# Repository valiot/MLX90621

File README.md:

### MLX90621 Arduino and Processing example code

Arduino and Processing code for the Melexis [MLX90621](http://www.melexis.com/Infrared-Thermometer-Sensors/Infrared-Thermometer-Sensors/Low-noise-high-speed-16x4-Far-Infrared-array-823.aspx) 16x4 thermopile array.

Includes R script to parse data files (which can be exported by Processing visualizer).

The MLX90621 FIRray temperature sensing device from Melexis utilizes the company’s non-contact temperature measurement technology to create a highly cost-effective thermography solution. Covering a -20°C to 300°C temperature range, this 16 x 4 element far infrared (FIR) thermopile sensor array produces a map of heat values for the target area in real time, avoiding the need to scan the area with a single point sensor or use an expensive microbolometer device.

In use in VU and Tilburg University temperature [cry detection project](http://www.pavlov.io/2015/07/01/detecting-crying-eyes/).

Implements MaxBot's MLX90621 [Arduino library](http://forum.arduino.cc/index.php?topic=126244.0) patched with KMoto's [minor change](http://forum.arduino.cc/index.php?topic=126244.msg2307588#msg2307588) in defaultConfig_H.

Also makes use of [nox771's i2c_t3 enhanced Teensy 3 Wire library](https://github.com/nox771/i2c_t3). This library allows a [Teensy 3.1](https://www.pjrc.com/store/teensy31.html) Arduino compatible USB development board to communicate with the MLX90621 over I2C/TWI.

TODO 2015-10-25: Refactor and clean up Processing visualizer.

##### Screenshot

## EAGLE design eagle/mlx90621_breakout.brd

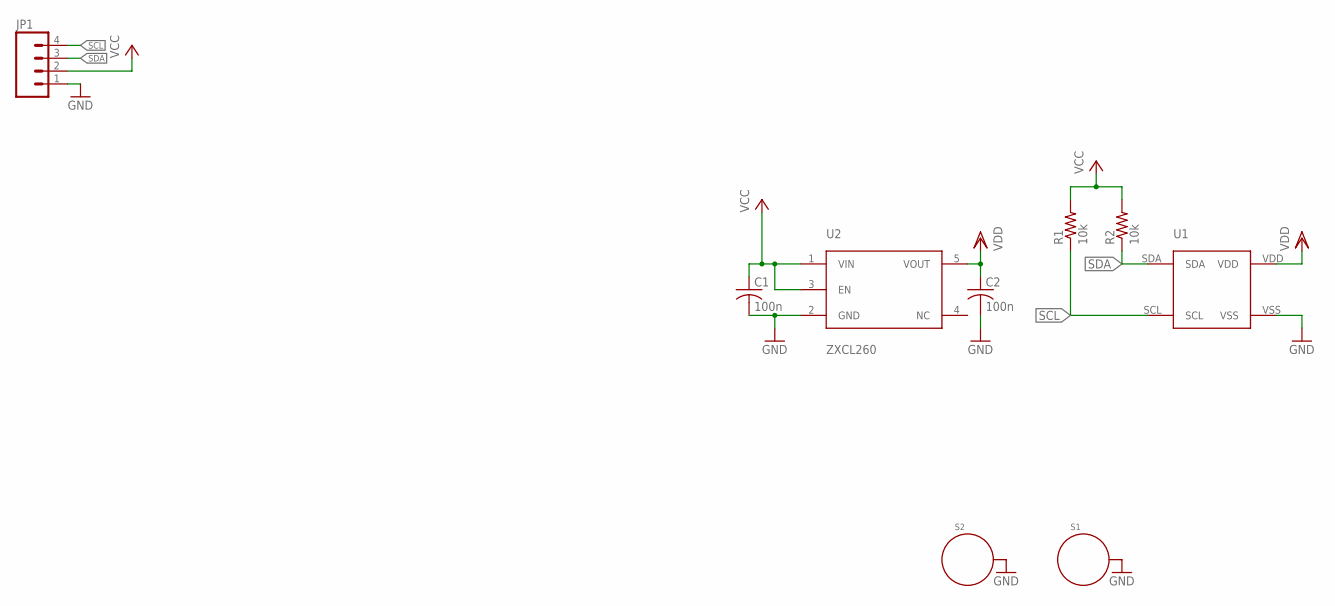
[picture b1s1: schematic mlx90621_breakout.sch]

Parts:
C1, C2: 100n; C0603
JP1: M04PTH; 1X04
R1, R2: 10k; R0603
S1, S2: STANDOFF_ELECTRICAL; STANDOFF-ELECTRICAL
U1: MLX90621BAD; MLX90621
U2: ZXCL260; VREG_SOT23-5

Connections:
GND: C1.2, C2.2, JP1.1, S1.P1, S2.P1, U1.VSS, U2.2 (GND)
SCL: JP1.4, R1.1, U1.SCL
SDA: JP1.3, R2.1, U1.SDA
VCC: C1.1, JP1.2, R1.2, R2.2, U2.1 (VIN), U2.3 (EN)
VDD: C2.1, U1.VDD, U2.5 (VOUT)

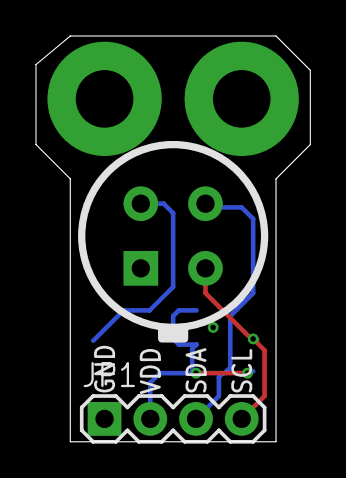
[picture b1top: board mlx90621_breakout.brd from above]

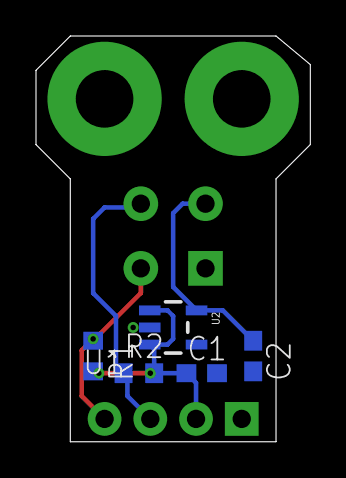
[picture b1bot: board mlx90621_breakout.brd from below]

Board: 2 copper layers, 15.2 x 22.5 mm, 9 parts (6 on the bottom side), 5 nets.

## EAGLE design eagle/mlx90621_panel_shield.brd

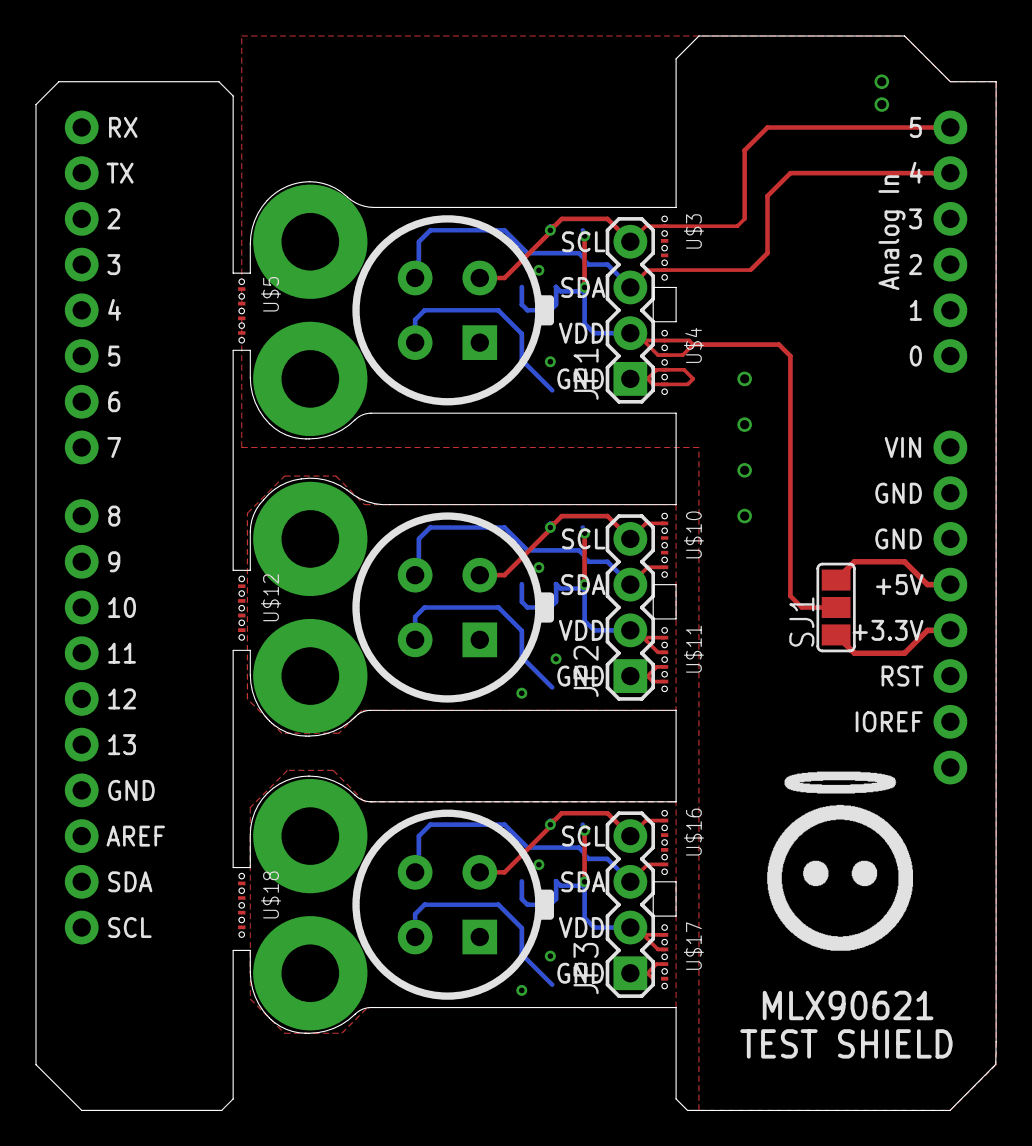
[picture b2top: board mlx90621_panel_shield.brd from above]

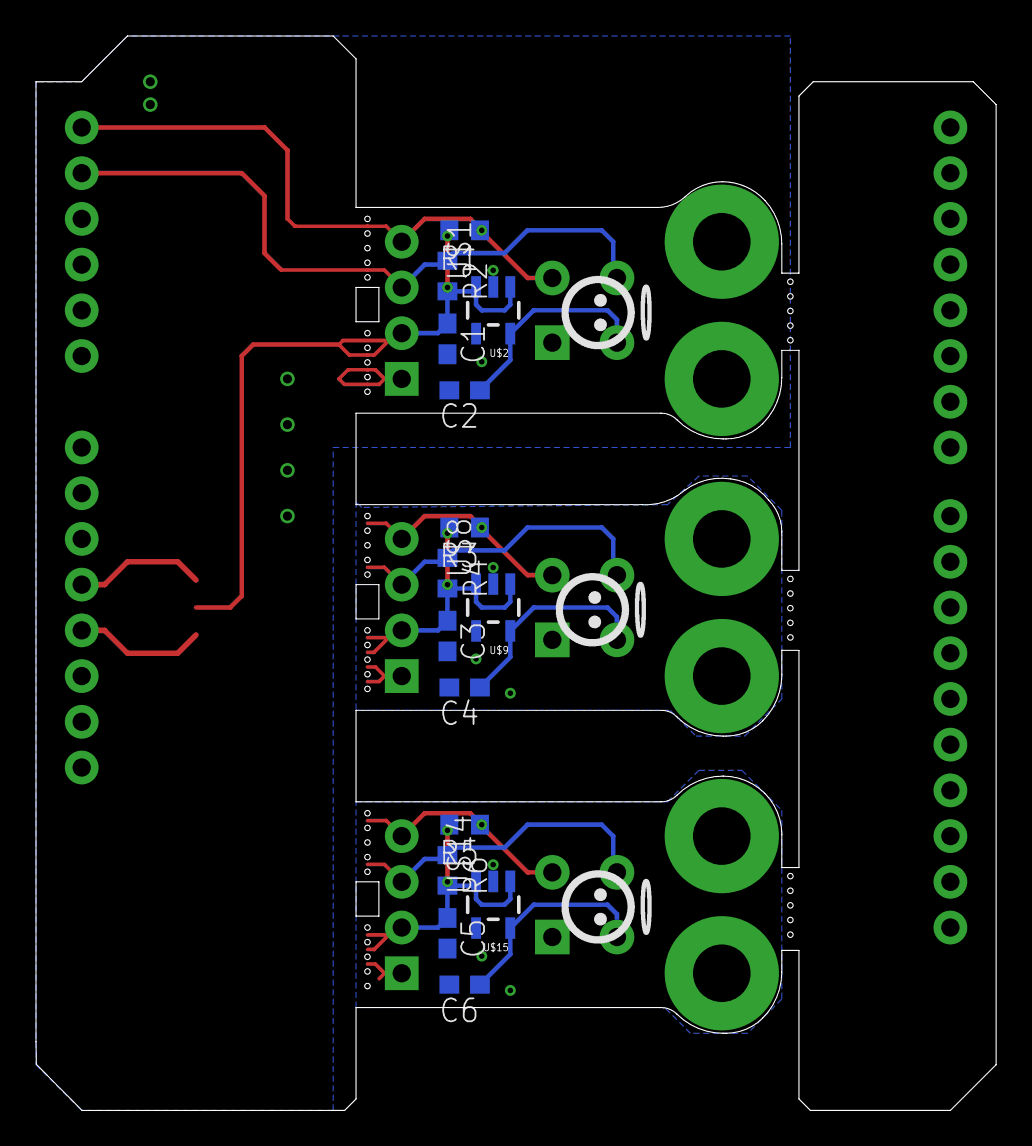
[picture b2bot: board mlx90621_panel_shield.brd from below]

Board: 2 copper layers, 53.3 x 59.7 mm, 42 parts (21 on the bottom side), 17 nets.

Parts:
C1, C2, C3, C4, C5, C6: 100n; C0603
E$1: DA_LOGO_10MM
E$2, E$3, E$4: DA_LOGO_5MM
J1: ARDUINO_R3_SHIELD; UNO_R3_SHIELD
JP1, JP2, JP3: 1X04
R1, R2, R3, R4, R5, R6: 10k; R0603
S1, S2, S3, S4, S5, S6: STANDOFF_ELECTRICAL; STANDOFF-ELECTRICAL
SJ1: SJ_2
U$1, U$8, U$14: MLX90621BAD; MLX90621
U$2, U$9, U$15: ZXCL260; VREG_SOT23-5
U$3, U$4, U$5, U$10, U$11, U$12, U$16, U$17, U$18: MOUSE-BITES-4

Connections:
+3V3: J1.3.3V, SJ1.1
+5V: J1.5V, SJ1.3
GND: C1.2, C2.2, J1.GND@0, J1.GND@1, JP1.1, S1.P1, S2.P1, U$1.VSS, U$2.2, U$4.3, U$4.4
GND1: C3.2, C4.2, JP2.1, S3.P1, S4.P1, U$8.VSS, U$9.2, U$11.3, U$11.4
GND2: C5.2, C6.2, JP3.1, S5.P1, S6.P1, U$14.VSS, U$15.2, U$17.3, U$17.4
SCL: J1.A5, JP1.4, R1.1, U$1.SCL, U$3.1
SCL1: JP2.4, R3.1, U$8.SCL, U$10.1
SCL2: JP3.4, R5.1, U$14.SCL, U$16.1
SDA: J1.A4, JP1.3, R2.1, U$1.SDA, U$3.4
SDA1: JP2.3, R4.1, U$8.SDA, U$10.4
SDA2: JP3.3, R6.1, U$14.SDA, U$16.4
VCC: C1.1, JP1.2, R1.2, R2.2, SJ1.2, U$2.1, U$2.3, U$4.1, U$4.2
VCC1: C3.1, JP2.2, R3.2, R4.2, U$9.1, U$9.3, U$11.1, U$11.2
VCC2: C5.1, JP3.2, R5.2, R6.2, U$15.1, U$15.3, U$17.1, U$17.2
VDD: C2.1, U$1.VDD, U$2.5
VDD1: C4.1, U$8.VDD, U$9.5
VDD2: C6.1, U$14.VDD, U$15.5

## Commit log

2017-08-20 Creada estructura del proyecto, basada en visualizador de ejemplo
2017-08-20 Modificado delay de Arduino
2017-08-20 Fix readme syntax
2017-08-21 Añadido gitignore
2017-08-21 modificado gitignore (Add jpg)
2017-08-22 Modificado readTemperatures por libreria de Longjos
2017-08-22 eliminado circuito de ejemplo incorrecto (jpg)
2017-08-22 Agregados a gitignore archivos backup de EAGLE
2017-08-23 Finalizado ruteo de MLX90621 en shield (x1)
2017-08-23 Finalizado diseño de panel shield
2017-08-23 añadida carpeta gerber a gitignore
2017-08-23 Añadida lib de logos de DA
2017-08-23 Añadidos logos a shield
2017-08-26 modificado .gitignore (ignorar gerbers de eagle)
2017-08-26 modificado .gitignore (ignora archivos gerber de eagle)
2017-08-27 Modificado baudrate en visualizador (ahora 115k2)
2017-08-27 Modificado baudrate en Arduino (ahora 115k2), modificados prints por blink de LED
2017-08-27 Añadida referencia para benchmark de funciones
2017-08-27 Modif libreria MLX para ir a 400kHz
2017-08-27 Tests de modificacion de resolucion a libreria (a mano)
2017-08-27 Correccion de factor K -> C (273.15) y prueba emisividad
2017-08-27 refactor checkConfig()
2017-08-28 Añadidas enumeraciones de resolucion y refresco a .h
2017-08-28 Añadidas propiedades y métodos de refresh, resolucion y emisividad a .h de sensor
2017-08-28 Implementados métodos de emisividad, refresh y resolucion en .cpp
2017-08-28 Actualizado ejemplo a nuevos métodos de la libreria de temperatura
2017-08-28 Modificado visualizador, ahora permite elegir rango de colores
2017-08-28 Mejorada visualizacion de gradiente
2017-08-28 Removida grasa de la interfaz (cuadros con promedios y umbrales)
2017-08-28 No guardar archivos por ahora y cambios en escala de color
2017-08-28 Eliminadas impresiones a serial innecesarias
2017-08-28 modificada resolucion de sensor de temperatura
2017-08-31 alarm visualizer
2017-08-31 Variables min mac configurables (teclas)
2017-09-12 Añadidas medidas a PCB
2017-09-12 Prueba de MOSFET vs calentador inductivo
2017-09-14 añadido BOM de eagle a gitignore
2017-09-14 eliminados archivos .txt innecesarios (outputs de visualizer)
2017-09-14 Eliminadas imports innecesarios del visualizador
2017-09-18 Prueba de corriente y PWM MOSFET
2017-09-18 Añadidas fotos de pruebas corriente
2017-09-23 Borrados archivos de tests de termopares (Movidos a otro repo)
2017-09-23 Modificado breakout de sensor MLX (Añadidos bValues)
2017-09-23 Modificada velocidad de comunicacion de sensor (4Hz a 8Hz)
2017-09-23 Modificada funcion de deteccion de puerto COM para aceptar puertos de Windows (COM)
2017-10-01 Add board image
2017-10-02 Add LICENSE
2017-10-07 añadido comentario inicial a headers
2017-10-08 prueba ems=0.1
2017-10-13 agregado linux a lista de sistemas soportados por el serial del visualizador
2017-10-14 emisividad 1.0
2018-05-21 cleaned PCB (Removed shield)
2018-05-21 cleaned board: Removed innecesary measures
2018-05-28 added measures and cleaned the board for clearer look
2018-05-28 cleaned breakout for better component counting at BOM generation
2018-05-28 changed References for ICs (U1, U2)
2018-05-28 updated gitignore: ignoring reference files (PDFs and stuff)
2018-06-06 Add pull request template

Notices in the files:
parts and their libraries:
SparkFun-Electromechanical: Licensing: Creative Commons ShareAlike 4.0 International - https://creativecommons.org/licenses/by-sa/4.0
